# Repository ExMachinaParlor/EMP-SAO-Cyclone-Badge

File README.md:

# EMP SAO Cyclone Badge

# Description
SAO with a simple arcade game similar to the classic Cyclone. Made to run on an ESP32-C3 and to interface with [Neopixel rings](https://www.adafruit.com/product/1463#technical-details).

# How to Play
## Attract Mode
A rotating purple LED on the outer ring and a slow blink of green on the inner ring is the default state
The SAO waits for a button press to transition to START_GAME

## Start Game
Resets the chasing light and randomly selects one of the LEDs to act as the target
Displays the jackpot briefly with a blue color. Immediately transitions to PLAY_GAME

## Play Game
A single lit LED moves around the outer ring.
The goal is to press the button when the active LED is over the previously displayed target LED

## Result
If the button is pressed when the active LED is on the target, it’s a win animation of flashing green
Otherwise, a lose animation of flashing red
After the animation the SAO returns to ATTRACT_MODE

# SAO BOM
- 1x [ESP32-C3 Nano](https://www.amazon.com/ESP32-C3-Development-Bluetooth-Running-Frequency/dp/B0DFWG87JS/?th=1)
- 1x [24 LED Neopixel ring](https://www.amazon.com/dp/B0B2D7742J)
- 1x [16 LED Neopixel ring](https://www.amazon.com/dp/B0B2D5QXG5)
- 2x [Push buttons](https://www.amazon.com/dp/B01CGMP9GY)
- 1x [2x3 0.1" Header pin box connector](https://www.amazon.com/gp/product/B00UBWKQLA/)
- 1x [SAO PCB](./PCB/EMP_Cyclone_SAO_v2/Gerber.zip)
- 8x 0.1" Header pins (Included in ESP32-C3 purchase)

# Flashing the Badge
- Use the arduino IDE
- Set board type to "nologo ESP32C3 Supermini"

# Future Work
- Add multiplayer mode
- Test with WLED and home assistant
- Use WiFi/BT to synchonize lights on multiple badges

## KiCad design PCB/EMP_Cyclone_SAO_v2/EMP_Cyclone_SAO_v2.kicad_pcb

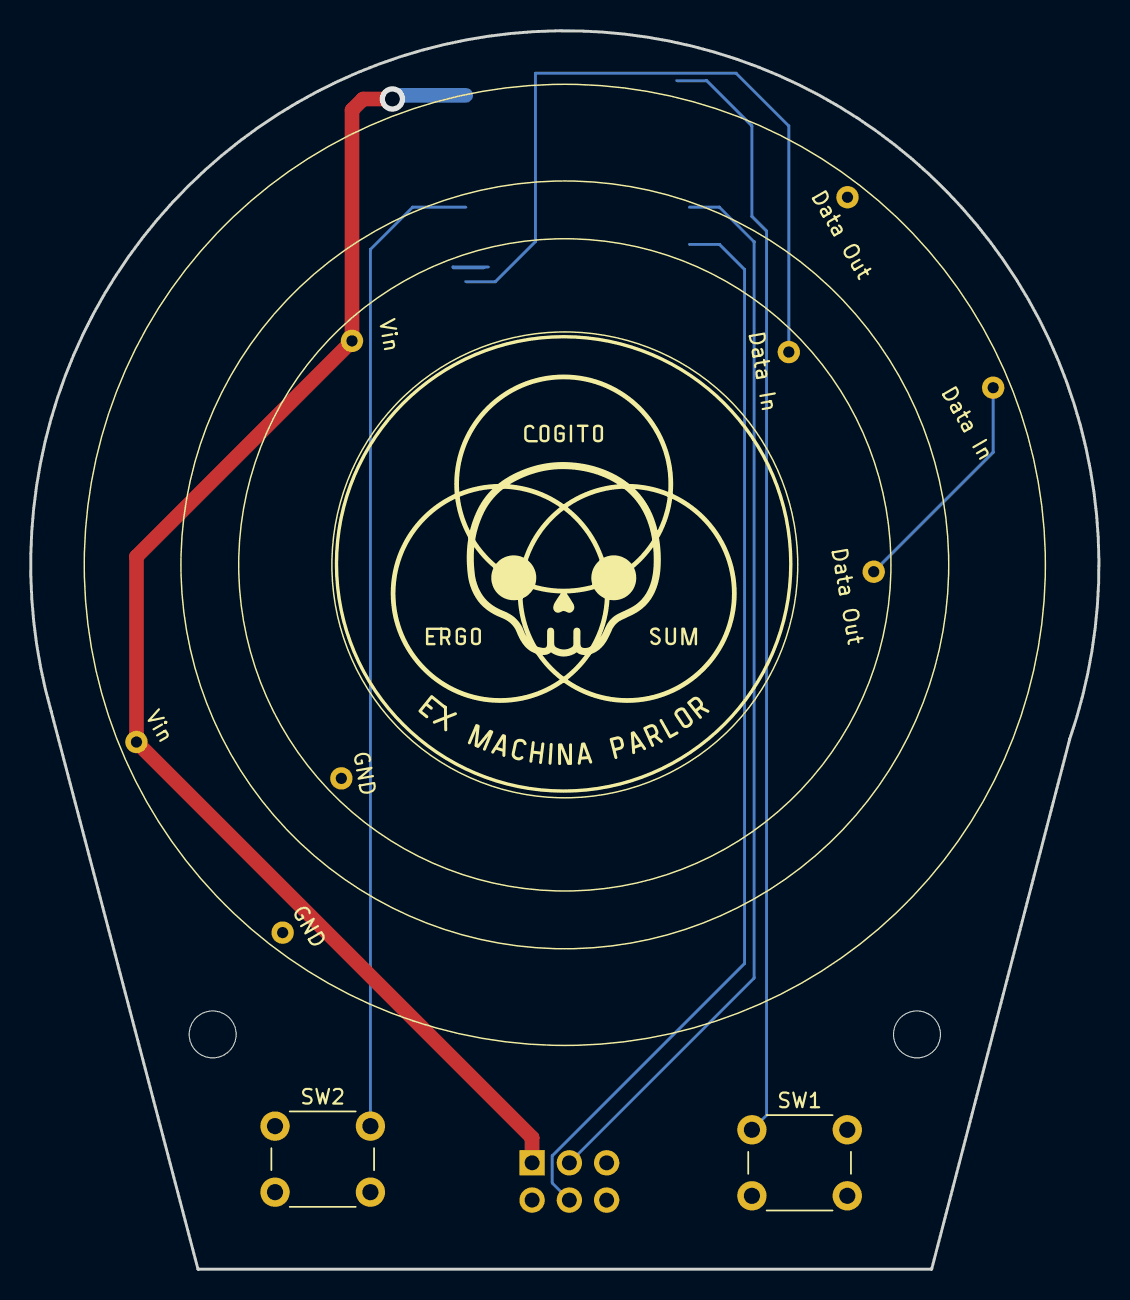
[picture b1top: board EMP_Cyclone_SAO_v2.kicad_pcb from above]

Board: 2 copper layers, 72.8 x 84.4 mm, 5 parts (1 on the bottom side), 5 nets.

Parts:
SW1, SW2: SW_Push; SW_PUSH_6mm
U1: Neopixel_Ring_16
U2: Neopixel_Ring_24
U3: ESP32-C3_SUPERMINI; MODULE_ESP32-C3_SUPERMINI

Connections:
+5V: U1.3, U2.3, U3.5V
GND: SW1.2, SW2.2, U1.4, U2.4, U3.G (GND)
unnamed: U1.1, U3.2 (GPIO2)
unnamed: SW2.1, U3.4 (GPIO4)
unnamed: SW1.1, U3.5 (GPIO5)

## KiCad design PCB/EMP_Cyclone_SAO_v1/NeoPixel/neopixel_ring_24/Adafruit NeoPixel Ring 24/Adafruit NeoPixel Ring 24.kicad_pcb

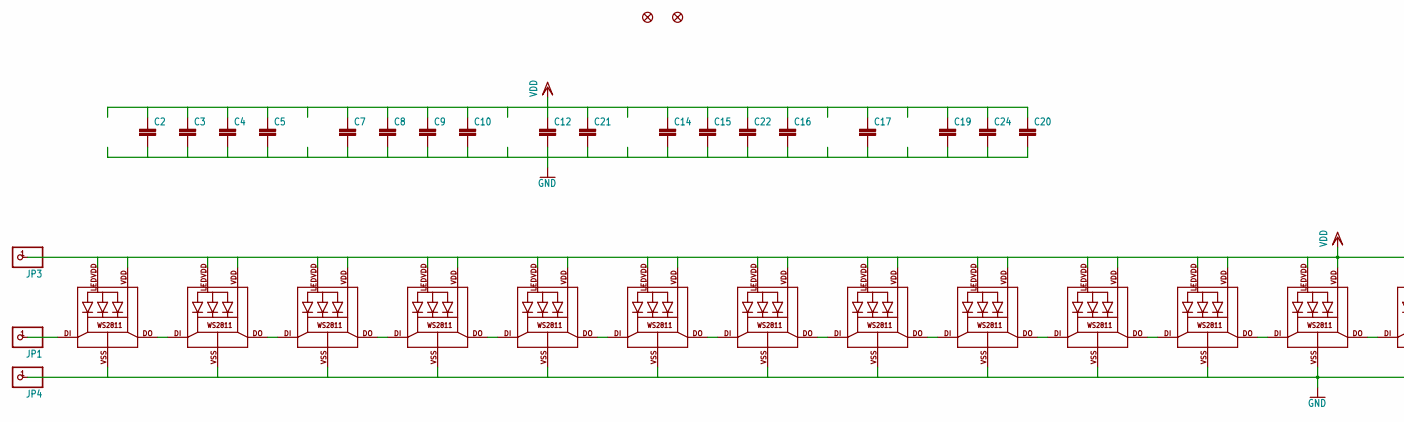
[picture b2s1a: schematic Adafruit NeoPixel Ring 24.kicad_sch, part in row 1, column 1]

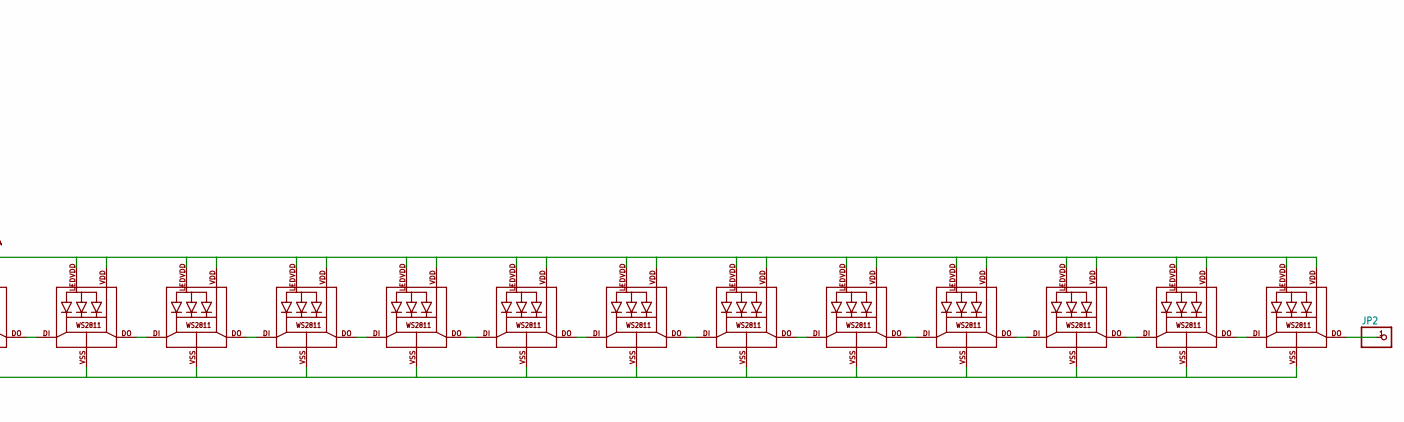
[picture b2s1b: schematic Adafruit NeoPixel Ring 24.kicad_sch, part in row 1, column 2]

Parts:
C2, C3, C4, C5, C7, C8, C9, C10, C12, C14, C15, C16, C17, C19, C20, C21, C22, C24: C-EUC0603; C0603
FID1, FID2: FIDUCIAL""; FIDUCIAL_1MM
JP1, JP2, JP3, JP4: PINHD-1X1CB; 1X01-CLEANBIG
LED1, LED2, LED3, LED4, LED5, LED6, LED7, LED8, LED9, LED10, LED11, LED12, LED13, LED14, LED15, LED16, LED17, LED18, LED19, LED20, LED21, LED22, LED23, LED24: WS28115050

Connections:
GND: C2.2, C3.2, C4.2, C5.2, C7.2, C8.2, C9.2, C10.2, C12.2, C14.2, C15.2, C16.2, C17.2, C19.2, C20.2, C21.2, C22.2, C24.2, JP4.1, LED1.VSS (GND), LED2.VSS (GND), LED3.VSS (GND), LED4.VSS (GND), LED5.VSS (GND), LED6.VSS (GND), LED7.VSS (GND), LED8.VSS (GND), LED9.VSS (GND), LED10.VSS (GND), LED11.VSS (GND), LED12.VSS (GND), LED13.VSS (GND), LED14.VSS (GND), LED15.VSS (GND), LED16.VSS (GND), LED17.VSS (GND), LED18.VSS (GND), LED19.VSS (GND), LED20.VSS (GND), LED21.VSS (GND), LED22.VSS (GND), LED23.VSS (GND), LED24.VSS (GND)
unnamed: LED1.DO, LED2.DI
unnamed: LED2.DO, LED3.DI
unnamed: LED3.DO, LED4.DI
unnamed: LED4.DO, LED5.DI
unnamed: LED5.DO, LED6.DI
unnamed: LED6.DO, LED7.DI
unnamed: LED7.DO, LED8.DI
unnamed: LED8.DO, LED9.DI
unnamed: LED9.DO, LED10.DI
unnamed: LED10.DO, LED11.DI
unnamed: LED11.DO, LED12.DI
unnamed: LED12.DO, LED13.DI
unnamed: LED13.DO, LED14.DI
unnamed: LED14.DO, LED15.DI
unnamed: LED15.DO, LED16.DI
unnamed: LED16.DO, LED17.DI
unnamed: LED17.DO, LED18.DI
unnamed: LED18.DO, LED19.DI
unnamed: LED19.DO, LED20.DI
unnamed: LED20.DO, LED21.DI
unnamed: LED21.DO, LED22.DI
unnamed: LED22.DO, LED23.DI
unnamed: LED23.DO, LED24.DI
unnamed: JP2.1, LED24.DO
unnamed: JP1.1, LED1.DI
VDD: C2.1, C3.1, C4.1, C5.1, C7.1, C8.1, C9.1, C10.1, C12.1, C14.1, C15.1, C16.1, C17.1, C19.1, C20.1, C21.1, C22.1, C24.1, JP3.1, LED1.LEDVDD, LED1.VDD, LED2.LEDVDD, LED2.VDD, LED3.LEDVDD, LED3.VDD, LED4.LEDVDD, LED4.VDD, LED5.LEDVDD, LED5.VDD, LED6.LEDVDD, LED6.VDD, LED7.LEDVDD, LED7.VDD, LED8.LEDVDD, LED8.VDD, LED9.LEDVDD, LED9.VDD, LED10.LEDVDD, LED10.VDD, LED11.LEDVDD, LED11.VDD, LED12.LEDVDD, LED12.VDD, LED13.LEDVDD, LED13.VDD, LED14.LEDVDD, LED14.VDD, LED15.LEDVDD, LED15.VDD, LED16.LEDVDD, LED16.VDD, LED17.LEDVDD, LED17.VDD, LED18.LEDVDD, LED18.VDD, LED19.LEDVDD, LED19.VDD, LED20.LEDVDD, LED20.VDD, LED21.LEDVDD, LED21.VDD, LED22.LEDVDD, LED22.VDD, LED23.LEDVDD, LED23.VDD, LED24.LEDVDD, LED24.VDD

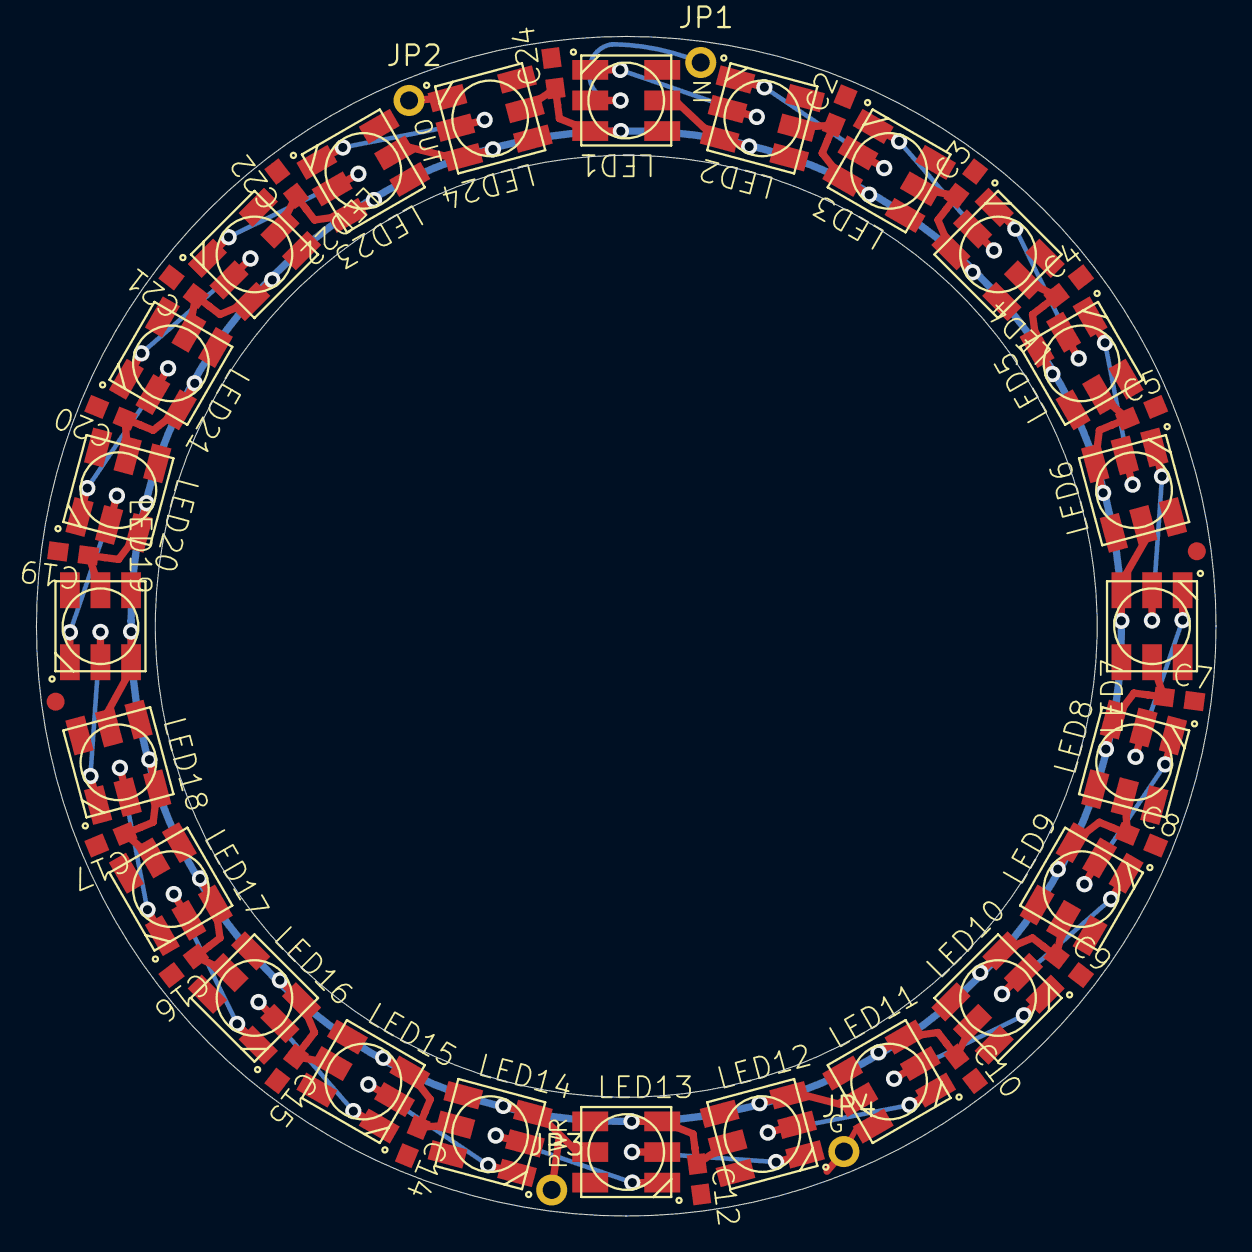
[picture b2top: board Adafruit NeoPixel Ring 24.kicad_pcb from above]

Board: 2 copper layers, 65.5 x 65.5 mm, 49 parts (1 on the bottom side), 27 nets.

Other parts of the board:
U$1: ADAFRUIT_5MM

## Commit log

2025-03-19 Initial build for Arduino Pro Mini
2025-03-19 Change number of lights on ring 1 and move button to pin 3
2025-03-19 added git for readme and created misc folder
2025-03-19 Added gif and description to readme
2025-03-19 Updated game to clearly show the target (jackpot) led before the start of each game
2025-03-20 Adding MVP EMP SAO PCB
    Minimum viable product defcon badge addon printed circuit board
2025-03-20 Add PNG of PCB
2025-03-20 Added teaser for SAO PCB in readme
2025-03-20 Upload missing kicad files
2025-03-21 v1. Updated silk screen on pcb. minor changes to traces. Updated gerber files.
2025-03-21 add new pcb image
2025-03-21 Update README with new PCB image and new gif location
2025-03-21 Add svg image
2025-03-29 Tested working on v1 PCB. Updated arduino sketch for pins used on v1 PCB. Minor updates to PCB silkscreen.
2025-04-20 Updated Gerber Files for the v1 PCB repo. The last commit had the correct kicad files but not updated gerber files.
2025-04-20 Added extraneous files to repo. Can probably trim some but better to have them uploaded and clean later.
2025-06-19 updated to use ESP32-C3 supermini
2025-06-19 v1.1 in progress with ESP32-C3 moved to back
2025-06-28 Update files in prep for moving repo
2025-07-13 mode to ESP32-C3 sumper mini (use nologo in arduino flasher). Upload arduino code to test on a single leg ring
2025-07-21 Final changes before moveing to EMP repo
2025-07-21 Updated readme. Cleaned up instructions on how to play. Added new BOM for SAOv2.
2025-07-21 fixed readme BOM link formatting
2025-07-21 EMP SAO v2.1. Gerber files updated and ordered.
2025-07-21 Update README.md with minimal flashing instructions
2025-07-21 Re-organized and cleaned up kicad files
2025-07-21 Fix BOM links and quantities
2025-07-21 Update README.md
    Added future work section
2025-07-28 Fix push button link on readme
2025-07-29 Second button now controls brightness with four levels. Badge starts on level 2 brightness
2025-07-30 Add Initial Build Instructions in PDF Form
2025-08-08 Add brightness control on second button
